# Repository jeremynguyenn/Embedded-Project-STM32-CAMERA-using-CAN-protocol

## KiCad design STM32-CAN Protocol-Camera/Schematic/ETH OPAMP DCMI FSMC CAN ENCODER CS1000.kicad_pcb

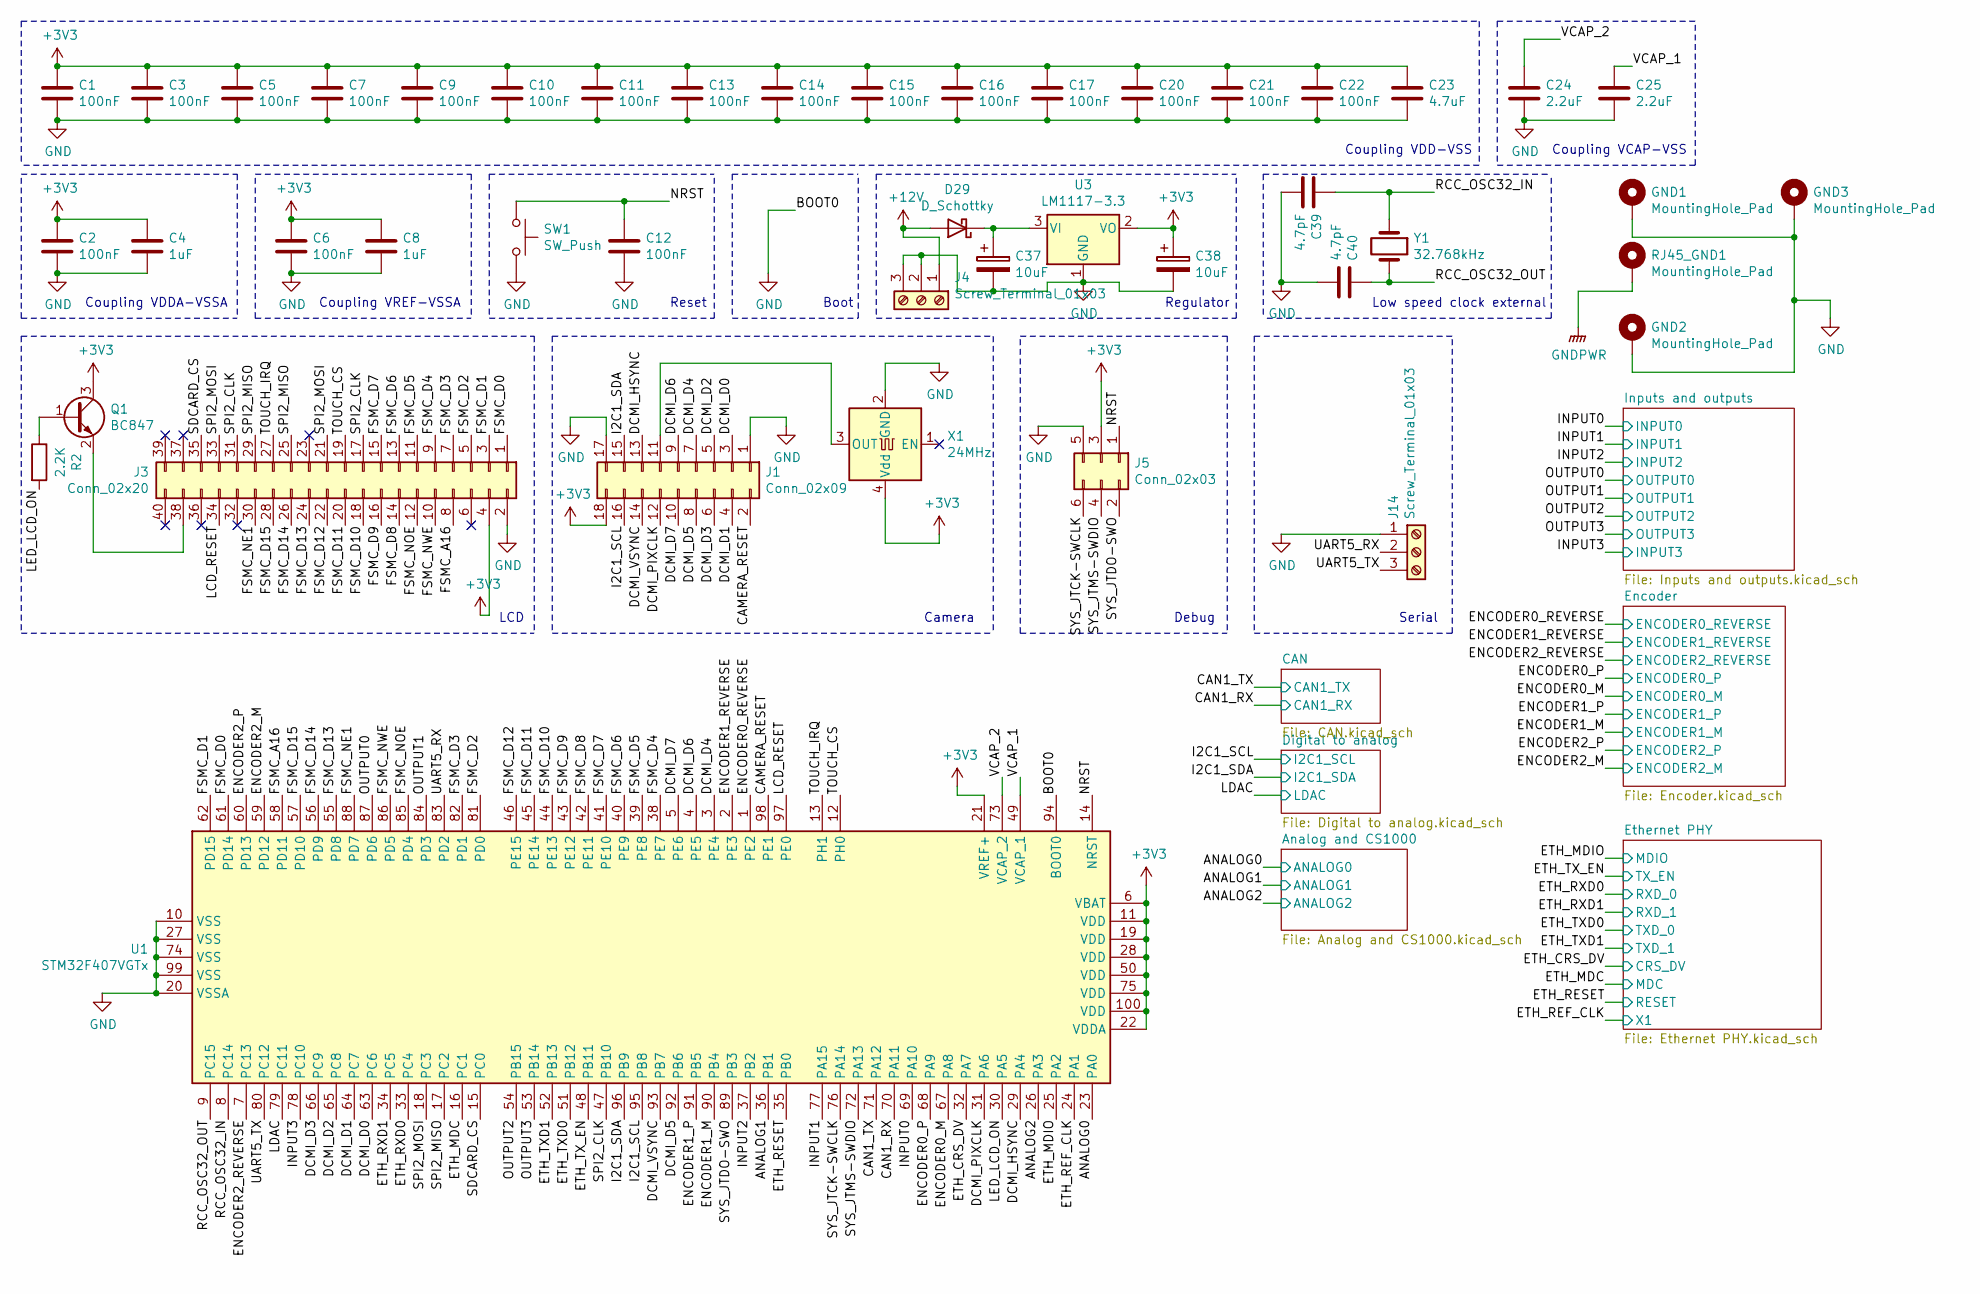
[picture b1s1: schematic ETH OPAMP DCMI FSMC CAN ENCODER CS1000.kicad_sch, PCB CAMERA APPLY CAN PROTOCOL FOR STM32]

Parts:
C1, C2, C3, C5, C6, C7, C9, C10, C11, C12, C13, C14, C15, C16, C17, C20, C21, C22: 100nF; C_0603_1608Metric
C4, C8: 1uF; C_0603_1608Metric
C23: 4.7uF; C_0603_1608Metric
C24, C25: 2.2uF; C_0603_1608Metric
C37, C38: 10uF; CP_EIA-1608-08_AVX-J_Pad1.25x1.05mm_HandSolder
C39, C40: 4.7pF; C_0603_1608Metric
D29: D_Schottky; D_SOD-123
GND1, GND2, GND3: MountingHole_Pad; MountingHole_2.7mm_M2.5_DIN965_Pad
J1: Conn_02x09; PinHeader_2x09_P2.54mm_Vertical
J3: Conn_02x20; PinHeader_2x20_P2.54mm_Vertical
J4, J14: Screw_Terminal_01x03; TerminalBlock_Phoenix_MKDS-1,5-3_1x03_P5.00mm_Horizontal
J5: Conn_02x03; PinHeader_2x03_P2.54mm_Vertical
Q1: BC847; SOT-23
R2: 2.2K; R_0603_1608Metric
RJ45_GND1: MountingHole_Pad; MountingHole_2.7mm_M2.5_DIN965_Pad
SW1: SW_Push; SW_SPST_FSMSM
U1: STM32F407VGTx; LQFP-100_14x14mm_P0.5mm
U3: LM1117-3.3; SOT-223
X1: 24MHz; Crystal_SMD_EuroQuartz_MT-4Pin_3.2x2.5mm_HandSoldering
Y1: 32.768kHz; Crystal_SMD_MicroCrystal_CC7V-T1A-2Pin_3.2x1.5mm_HandSolder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

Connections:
+3V3: C1.1, C2.1, C3.1, C4.1, C5.1, C6.1, C7.1, C8.1, C9.1, C10.1, C11.1, C13.1, C14.1, C15.1, C16.1, C17.1, C20.1, C21.1, C22.1, C23.1, C38.1, J1.18, J3.4, J5.3, Q1.3 (C), U1.6 (VBAT), U1.11 (VDD), U1.19 (VDD), U1.21 (VREF+), U1.22 (VDDA), U1.28 (VDD), U1.50 (VDD), U1.75 (VDD), U1.100 (VDD), U3.2 (VO), X1.4 (Vdd); also elsewhere on the board
+12V: D29.2 (A), J4.1
/ANALOG0: U1.23 (PA0); also elsewhere on the board
/ANALOG1: U1.36 (PB1); also elsewhere on the board
/ANALOG2: U1.26 (PA3); also elsewhere on the board
/CAMERA_RESET: J1.2, U1.98 (PE1)
/CAN1_RX: U1.70 (PA11); also elsewhere on the board
/CAN1_TX: U1.71 (PA12); also elsewhere on the board
/DCMI_D0: J1.3, U1.63 (PC6)
/DCMI_D1: J1.4, U1.64 (PC7)
/DCMI_D2: J1.5, U1.65 (PC8)
/DCMI_D3: J1.6, U1.66 (PC9)
/DCMI_D4: J1.7, U1.3 (PE4)
/DCMI_D5: J1.8, U1.92 (PB6)
/DCMI_D6: J1.9, U1.4 (PE5)
/DCMI_D7: J1.10, U1.5 (PE6)
/DCMI_HSYNC: J1.13, U1.29 (PA4)
/DCMI_PIXCLK: J1.12, U1.31 (PA6)
/DCMI_VSYNC: J1.14, U1.93 (PB7)
/ENCODER0_M: U1.67 (PA8); also elsewhere on the board
/ENCODER0_P: U1.68 (PA9); also elsewhere on the board
/ENCODER0_REVERSE: U1.1 (PE2); also elsewhere on the board
/ENCODER1_M: U1.90 (PB4); also elsewhere on the board
/ENCODER1_P: U1.91 (PB5); also elsewhere on the board
/ENCODER1_REVERSE: U1.2 (PE3); also elsewhere on the board
/ENCODER2_M: U1.59 (PD12); also elsewhere on the board
/ENCODER2_P: U1.60 (PD13); also elsewhere on the board
/ENCODER2_REVERSE: U1.7 (PC13); also elsewhere on the board
/ETH_CRS_DV: U1.32 (PA7); also elsewhere on the board
/ETH_MDC: U1.16 (PC1); also elsewhere on the board
/ETH_MDIO: U1.25 (PA2); also elsewhere on the board
/ETH_REF_CLK: U1.24 (PA1); also elsewhere on the board
/ETH_RESET: U1.35 (PB0); also elsewhere on the board
/ETH_RXD0: U1.33 (PC4); also elsewhere on the board
/ETH_RXD1: U1.34 (PC5); also elsewhere on the board
/ETH_TXD0: U1.51 (PB12); also elsewhere on the board
/ETH_TXD1: U1.52 (PB13); also elsewhere on the board
/ETH_TX_EN: U1.48 (PB11); also elsewhere on the board
/FSMC_A16: J3.8, U1.58 (PD11)
/FSMC_D0: J3.1, U1.61 (PD14)
/FSMC_D1: J3.3, U1.62 (PD15)
/FSMC_D2: J3.5, U1.81 (PD0)
/FSMC_D3: J3.7, U1.82 (PD1)
/FSMC_D4: J3.9, U1.38 (PE7)
/FSMC_D5: J3.11, U1.39 (PE8)
/FSMC_D6: J3.13, U1.40 (PE9)
/FSMC_D7: J3.15, U1.41 (PE10)
/FSMC_D8: J3.14, U1.42 (PE11)
/FSMC_D9: J3.16, U1.43 (PE12)
/FSMC_D10: J3.18, U1.44 (PE13)
/FSMC_D11: J3.20, U1.45 (PE14)
/FSMC_D12: J3.22, U1.46 (PE15)
/FSMC_D13: J3.24, U1.55 (PD8)
/FSMC_D14: J3.26, U1.56 (PD9)
/FSMC_D15: J3.28, U1.57 (PD10)
/FSMC_NE1: J3.30, U1.88 (PD7)
/FSMC_NOE: J3.12, U1.85 (PD4)
/FSMC_NWE: J3.10, U1.86 (PD5)
/I2C1_SCL: J1.16, U1.95 (PB8); also elsewhere on the board
/I2C1_SDA: J1.15, U1.96 (PB9); also elsewhere on the board
/INPUT0: U1.69 (PA10); also elsewhere on the board
/INPUT1: U1.77 (PA15); also elsewhere on the board
/INPUT2: U1.37 (PB2); also elsewhere on the board
/INPUT3: U1.78 (PC10); also elsewhere on the board
/LCD_RESET: J3.34, U1.97 (PE0)
/LDAC: U1.79 (PC11); also elsewhere on the board
/LED_LCD_ON: R2.2, U1.30 (PA5)
/NRST: C12.1, J5.1, SW1.1, U1.14 (NRST)
/OUTPUT0: U1.87 (PD6); also elsewhere on the board
/OUTPUT1: U1.84 (PD3); also elsewhere on the board
/OUTPUT2: U1.54 (PB15); also elsewhere on the board
/OUTPUT3: U1.53 (PB14); also elsewhere on the board
/RCC_OSC32_IN: C39.1, U1.8 (PC14), Y1.1
/RCC_OSC32_OUT: C40.1, U1.9 (PC15), Y1.2
/SDCARD_CS: J3.35, U1.15 (PC0)
/SPI2_CLK: J3.17, J3.31, U1.47 (PB10)
/SPI2_MISO: J3.25, J3.29, U1.17 (PC2)
/SPI2_MOSI: J3.21, J3.33, U1.18 (PC3)
/SYS_JTCK-SWCLK: J5.6, U1.76 (PA14)
/SYS_JTDO-SWO: J5.2, U1.89 (PB3)
/SYS_JTMS-SWDIO: J5.4, U1.72 (PA13)
/TOUCH_CS: J3.19, U1.12 (PH0)
/TOUCH_IRQ: J3.27, U1.13 (PH1)
/UART5_RX: J14.2, U1.83 (PD2)
/UART5_TX: J14.3, U1.80 (PC12)
/VCAP_1: C25.1, U1.49 (VCAP_1)
/VCAP_2: C24.1, U1.73 (VCAP_2)
GND: C1.2, C2.2, C3.2, C4.2, C5.2, C6.2, C7.2, C8.2, C9.2, C10.2, C11.2, C12.2, C13.2, C14.2, C15.2, C16.2, C17.2, C20.2, C21.2, C22.2, C23.2, C24.2, C25.2, C37.2, C38.2, C39.2, C40.2, GND1.1, GND2.1, GND3.1, J1.1, J1.17, J3.2, J4.2, J4.3, J5.5, J14.1, SW1.2, U1.10 (VSS), U1.20 (VSSA), U1.27 (VSS), U1.74 (VSS), U1.94 (BOOT0), U1.99 (VSS), U3.1 (GND), X1.2 (GND); also elsewhere on the board
GNDPWR: RJ45_GND1.1; also elsewhere on the board
unnamed: C37.1, D29.1 (K), U3.3 (VI)
unnamed: J1.11, X1.3 (OUT)
unnamed: J3.38, Q1.2 (E)
unnamed: Q1.1 (B), R2.1

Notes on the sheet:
Coupling VREF-VSSA
Camera
Boot
Low speed clock external
Regulator
Coupling VDD-VSS
Coupling VDDA-VSSA
Serial
LCD
Coupling VCAP-VSS
Reset
Debug

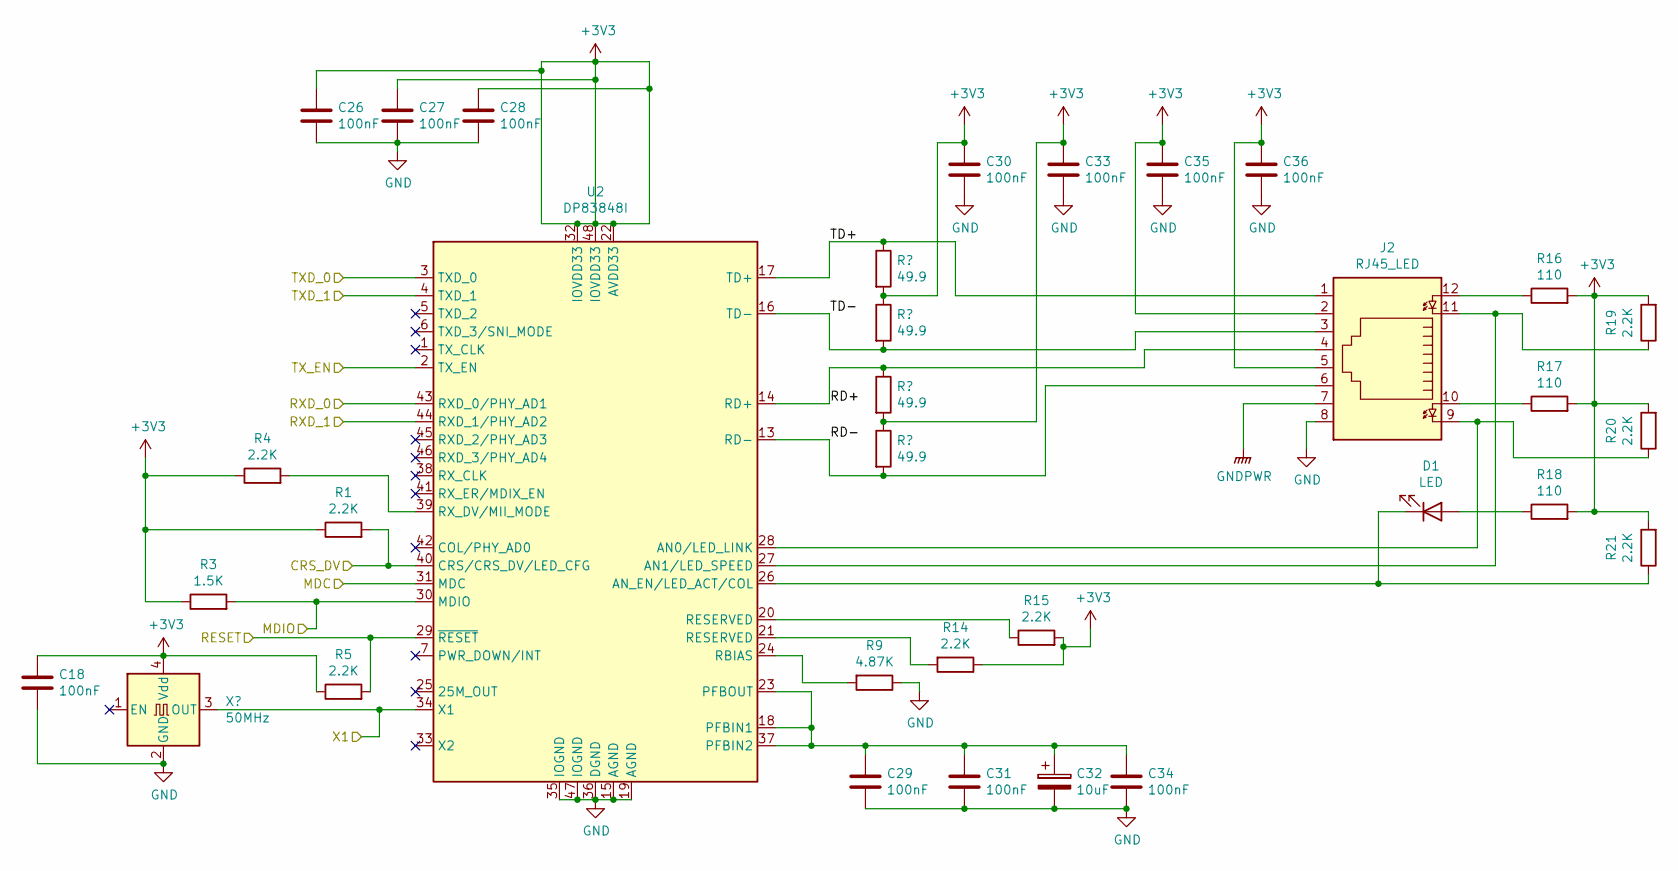
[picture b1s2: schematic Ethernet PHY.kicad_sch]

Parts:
C18, C26, C27, C28, C29, C30, C31, C33, C34, C35, C36: 100nF; C_0603_1608Metric
C32: 10uF; CP_EIA-1608-08_AVX-J_Pad1.25x1.05mm_HandSolder
D1: LED; LED_0603_1608Metric
J2: RJ45_LED; RJ45_Wuerth_7499010121A_Horizontal
R1, R4, R5, R14, R15, R19, R20, R21: 2.2K; R_0603_1608Metric
R3: 1.5K; R_0603_1608Metric
R9: 4.87K; R_0603_1608Metric
R10, R11, R12, R13: 49.9; R_0603_1608Metric
R16, R17, R18: 110; R_0603_1608Metric
U2: DP83848I; LQFP-48_7x7mm_P0.5mm
X2: 50MHz; Crystal_SMD_EuroQuartz_MT-4Pin_3.2x2.5mm_HandSoldering

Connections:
+3V3: C18.1, C26.1, C27.1, C28.1, C30.1, C33.1, C35.1, C36.1, J2.2, J2.5, R1.1, R3.1, R4.1, R5.1, R10.2, R11.1, R12.2, R13.1, R14.1, R15.2, R16.2, R17.2, R18.2, R19.2, R20.2, R21.2, U2.22 (AVDD33), U2.32 (IOVDD33), U2.48 (IOVDD33), X2.4 (Vdd); also elsewhere on the board
/ETH_CRS_DV: R1.2, U2.40 (CRS/CRS_DV/LED_CFG); also elsewhere on the board
/ETH_MDC: U2.31 (MDC); also elsewhere on the board
/ETH_MDIO: R3.2, U2.30 (MDIO); also elsewhere on the board
/ETH_REF_CLK: U2.34 (X1), X2.3 (OUT); also elsewhere on the board
/ETH_RESET: R5.2, U2.29 (~RESET); also elsewhere on the board
/ETH_RXD0: U2.43 (RXD_0/PHY_AD1); also elsewhere on the board
/ETH_RXD1: U2.44 (RXD_1/PHY_AD2); also elsewhere on the board
/ETH_TXD0: U2.3 (TXD_0); also elsewhere on the board
/ETH_TXD1: U2.4 (TXD_1); also elsewhere on the board
/ETH_TX_EN: U2.2 (TX_EN); also elsewhere on the board
/Ethernet PHY/RD+: J2.4, R12.1, U2.14 (RD+)
/Ethernet PHY/RD-: J2.6, R13.2, U2.13 (RD-)
/Ethernet PHY/TD+: J2.1, R10.1, U2.17 (TD+)
/Ethernet PHY/TD-: J2.3, R11.2, U2.16 (TD-)
GND: C18.2, C26.2, C27.2, C28.2, C29.2, C30.2, C31.2, C32.2, C33.2, C34.2, C35.2, C36.2, J2.8, R9.1, U2.15 (AGND), U2.19 (AGND), U2.35 (IOGND), U2.36 (DGND), U2.47 (IOGND), X2.2 (GND); also elsewhere on the board
GNDPWR: J2.7; also elsewhere on the board
unnamed: C29.1, C31.1, C32.1, C34.1, U2.18 (PFBIN1), U2.23 (PFBOUT), U2.37 (PFBIN2)
unnamed: D1.1 (K), R21.1, U2.26 (AN_EN/LED_ACT/COL)
unnamed: D1.2 (A), R18.1
unnamed: J2.9, R20.1, U2.28 (AN0/LED_LINK)
unnamed: J2.10, R17.1
unnamed: J2.11, R19.1, U2.27 (AN1/LED_SPEED)
unnamed: J2.12, R16.1
unnamed: R4.2, U2.39 (RX_DV/MII_MODE)
unnamed: R9.2, U2.24 (RBIAS)
unnamed: R14.2, U2.21 (RESERVED)
unnamed: R15.1, U2.20 (RESERVED)

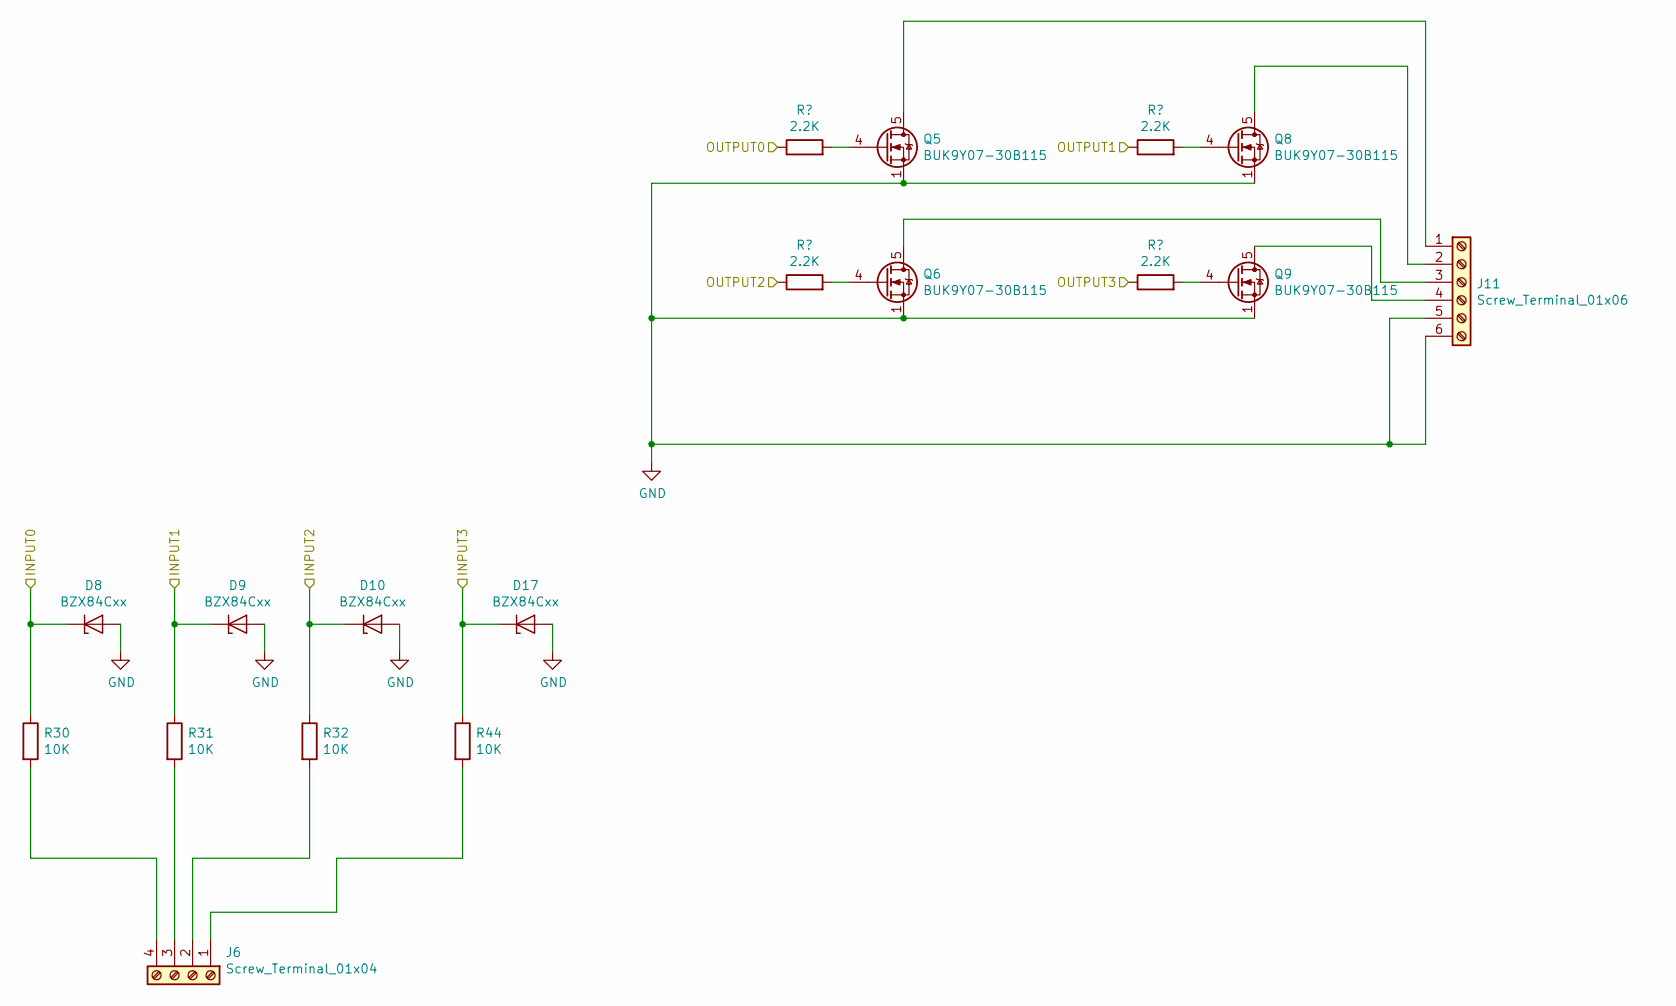
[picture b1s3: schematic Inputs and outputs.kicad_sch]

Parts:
D8, D9, D10, D17: BZX84Cxx; D_SOT-23_ANK
J6: Screw_Terminal_01x04; TerminalBlock_Phoenix_MKDS-1,5-4_1x04_P5.00mm_Horizontal
J11: Screw_Terminal_01x06; TerminalBlock_Phoenix_MKDS-1,5-6_1x06_P5.00mm_Horizontal
Q5, Q6, Q8, Q9: BUK9Y07-30B115; LFPAK56
R30, R31, R32, R44: 10K; R_0603_1608Metric
R33, R34, R36, R37: 2.2K; R_0603_1608Metric

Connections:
/INPUT0: D8.1 (K), R30.1; also elsewhere on the board
/INPUT1: D9.1 (K), R31.1; also elsewhere on the board
/INPUT2: D10.1 (K), R32.1; also elsewhere on the board
/INPUT3: D17.1 (K), R44.1; also elsewhere on the board
/OUTPUT0: R33.1; also elsewhere on the board
/OUTPUT1: R36.1; also elsewhere on the board
/OUTPUT2: R34.1; also elsewhere on the board
/OUTPUT3: R37.1; also elsewhere on the board
GND: D8.2 (A), D9.2 (A), D10.2 (A), D17.2 (A), J11.5, J11.6, Q5.1 (S), Q5.2 (S), Q5.3 (S), Q6.1 (S), Q6.2 (S), Q6.3 (S), Q8.1 (S), Q8.2 (S), Q8.3 (S), Q9.1 (S), Q9.2 (S), Q9.3 (S); also elsewhere on the board
unnamed: J6.1, R44.2
unnamed: J6.2, R32.2
unnamed: J6.3, R31.2
unnamed: J6.4, R30.2
unnamed: J11.1, Q5.5 (D)
unnamed: J11.2, Q8.5 (D)
unnamed: J11.3, Q6.5 (D)
unnamed: J11.4, Q9.5 (D)
unnamed: Q5.4 (G), R33.2
unnamed: Q6.4 (G), R34.2
unnamed: Q8.4 (G), R36.2
unnamed: Q9.4 (G), R37.2

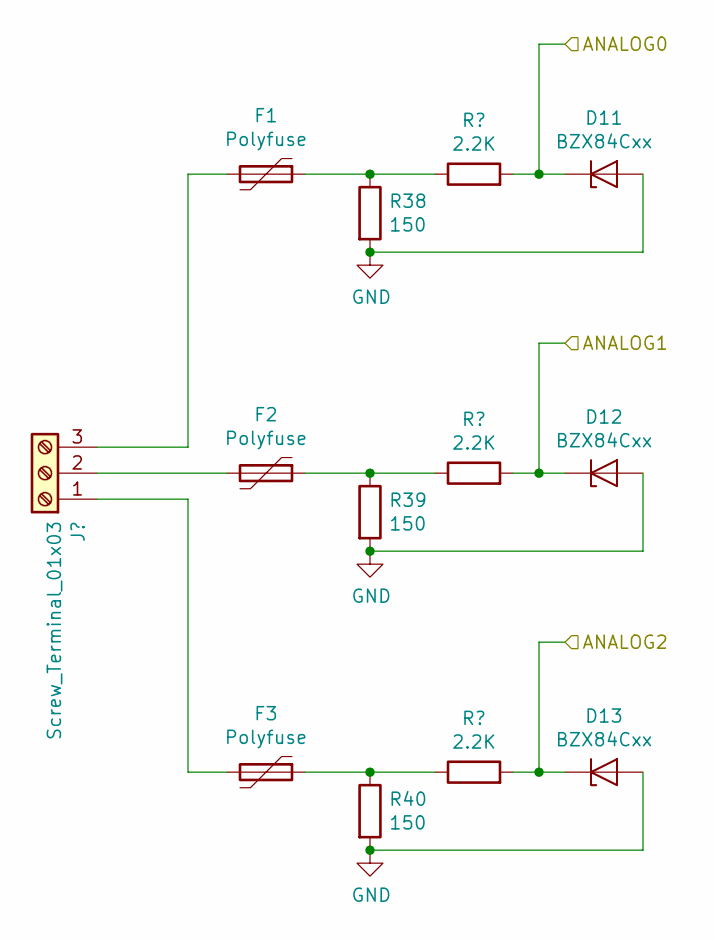
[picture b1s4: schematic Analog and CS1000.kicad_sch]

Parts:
D11, D12, D13: BZX84Cxx; D_SOT-23_ANK
F1, F2, F3: Polyfuse; R_0603_1608Metric
J12: Screw_Terminal_01x03; TerminalBlock_Phoenix_MKDS-1,5-3_1x03_P5.00mm_Horizontal
R38, R39, R40: 150; R_1206_3216Metric
R41, R42, R43: 2.2K; R_0603_1608Metric

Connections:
/ANALOG0: D11.1 (K), R41.2; also elsewhere on the board
/ANALOG1: D12.1 (K), R42.2; also elsewhere on the board
/ANALOG2: D13.1 (K), R43.2; also elsewhere on the board
GND: D11.2 (A), D12.2 (A), D13.2 (A), R38.2, R39.2, R40.2; also elsewhere on the board
unnamed: F1.1, R38.1, R41.1
unnamed: F1.2, J12.3
unnamed: F2.1, R39.1, R42.1
unnamed: F2.2, J12.2
unnamed: F3.1, R40.1, R43.1
unnamed: F3.2, J12.1

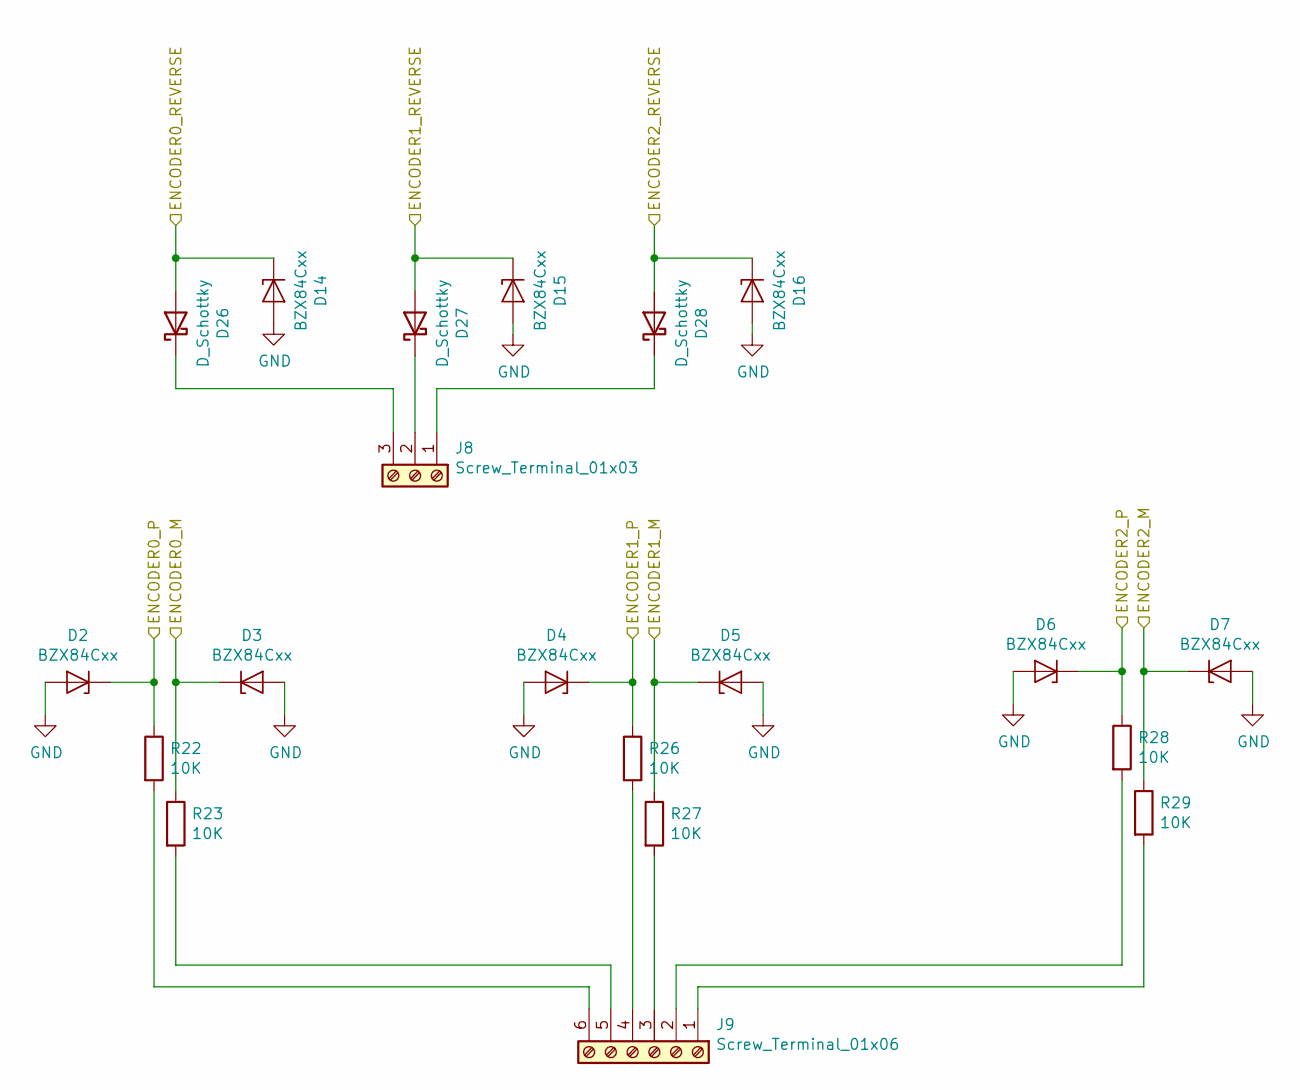
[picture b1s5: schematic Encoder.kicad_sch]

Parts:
D2, D3, D4, D5, D6, D7, D14, D15, D16: BZX84Cxx; D_SOT-23_ANK
D26, D27, D28: D_Schottky; D_SOD-123
J8: Screw_Terminal_01x03; TerminalBlock_Phoenix_MKDS-1,5-3_1x03_P5.00mm_Horizontal
J9: Screw_Terminal_01x06; TerminalBlock_Phoenix_MKDS-1,5-6_1x06_P5.00mm_Horizontal
R22, R23, R26, R27, R28, R29: 10K; R_0603_1608Metric

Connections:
/ENCODER0_M: D3.1 (K), R23.1; also elsewhere on the board
/ENCODER0_P: D2.1 (K), R22.1; also elsewhere on the board
/ENCODER0_REVERSE: D14.1 (K), D26.2 (A); also elsewhere on the board
/ENCODER1_M: D5.1 (K), R27.1; also elsewhere on the board
/ENCODER1_P: D4.1 (K), R26.1; also elsewhere on the board
/ENCODER1_REVERSE: D15.1 (K), D27.2 (A); also elsewhere on the board
/ENCODER2_M: D7.1 (K), R29.1; also elsewhere on the board
/ENCODER2_P: D6.1 (K), R28.1; also elsewhere on the board
/ENCODER2_REVERSE: D16.1 (K), D28.2 (A); also elsewhere on the board
GND: D2.2 (A), D3.2 (A), D4.2 (A), D5.2 (A), D6.2 (A), D7.2 (A), D14.2 (A), D15.2 (A), D16.2 (A); also elsewhere on the board
unnamed: D26.1 (K), J8.3
unnamed: D27.1 (K), J8.2
unnamed: D28.1 (K), J8.1
unnamed: J9.1, R29.2
unnamed: J9.2, R28.2
unnamed: J9.3, R27.2
unnamed: J9.4, R26.2
unnamed: J9.5, R23.2
unnamed: J9.6, R22.2

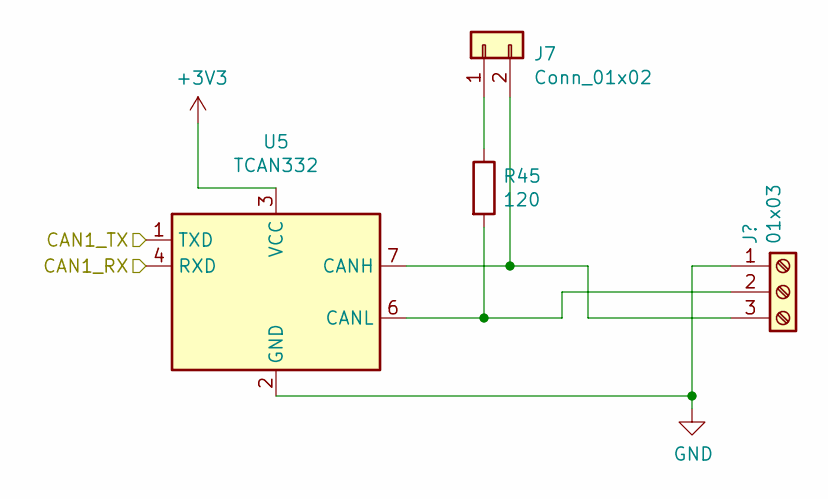
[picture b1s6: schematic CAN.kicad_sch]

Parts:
J7: Conn_01x02; PinHeader_1x02_P2.54mm_Vertical
J10: 01x03; TerminalBlock_Phoenix_MKDS-1,5-3_1x03_P5.00mm_Horizontal
R45: 120; R_0603_1608Metric
U5: TCAN332; SOIC-8_3.9x4.9mm_P1.27mm

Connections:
+3V3: U5.3 (VCC); also elsewhere on the board
/CAN1_RX: U5.4 (RXD); also elsewhere on the board
/CAN1_TX: U5.1 (TXD); also elsewhere on the board
GND: J10.1, U5.2 (GND); also elsewhere on the board
unnamed: J7.1, R45.1
unnamed: J10.2, R45.2, U5.6 (CANL)
unnamed: J7.2, J10.3, U5.7 (CANH)

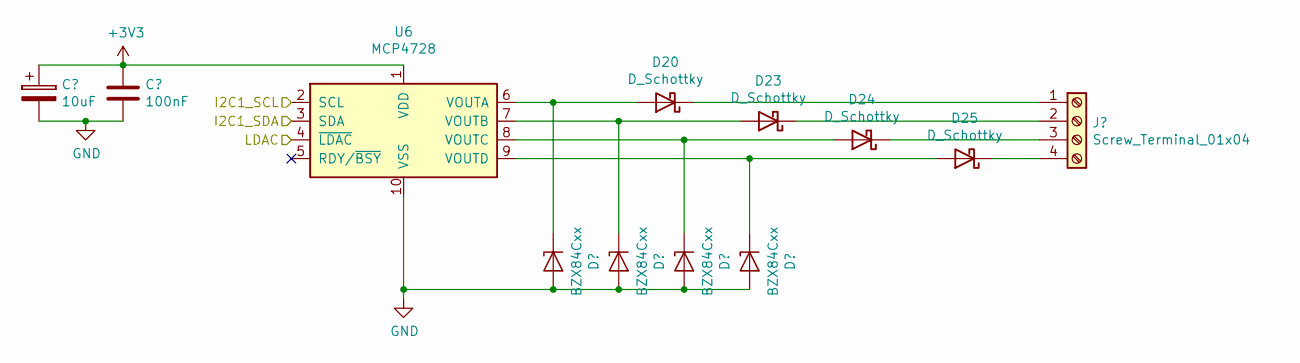
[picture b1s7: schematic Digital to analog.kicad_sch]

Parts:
C41: 10uF; CP_EIA-1608-08_AVX-J_Pad1.25x1.05mm_HandSolder
C42: 100nF; C_0603_1608Metric
D18, D19, D21, D22: BZX84Cxx; D_SOT-23_ANK
D20, D23, D24, D25: D_Schottky; D_SOD-123
J13: Screw_Terminal_01x04; TerminalBlock_Phoenix_MKDS-1,5-4_1x04_P5.00mm_Horizontal
U6: MCP4728; MSOP-10_3x3mm_P0.5mm

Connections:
+3V3: C41.1, C42.1, U6.1 (VDD); also elsewhere on the board
/I2C1_SCL: U6.2 (SCL); also elsewhere on the board
/I2C1_SDA: U6.3 (SDA); also elsewhere on the board
/LDAC: U6.4 (~LDAC); also elsewhere on the board
GND: C41.2, C42.2, D18.2 (A), D19.2 (A), D21.2 (A), D22.2 (A), U6.10 (VSS); also elsewhere on the board
unnamed: D18.1 (K), D20.2 (A), U6.6 (VOUTA)
unnamed: D19.1 (K), D23.2 (A), U6.7 (VOUTB)
unnamed: D20.1 (K), J13.1
unnamed: D21.1 (K), D24.2 (A), U6.8 (VOUTC)
unnamed: D22.1 (K), D25.2 (A), U6.9 (VOUTD)
unnamed: D23.1 (K), J13.2
unnamed: D24.1 (K), J13.3
unnamed: D25.1 (K), J13.4

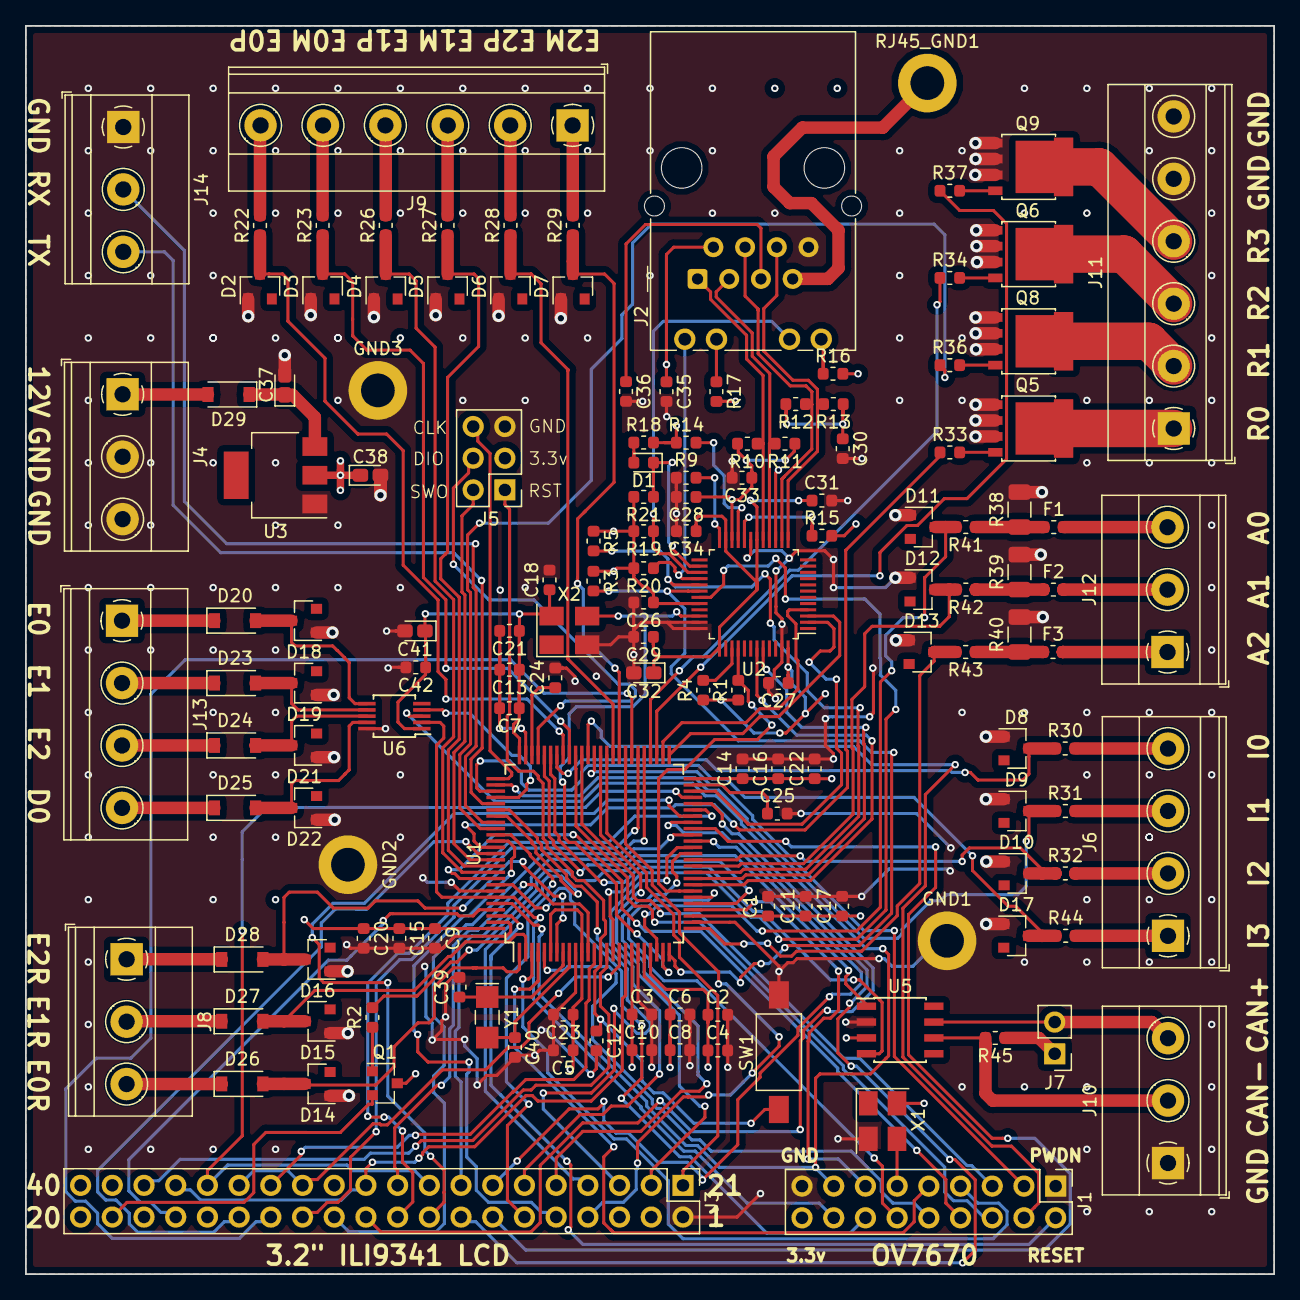
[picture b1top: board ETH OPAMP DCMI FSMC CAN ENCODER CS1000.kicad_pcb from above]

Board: 4 copper layers, 100.0 x 100.0 mm, 144 parts (0 on the bottom side), 146 nets.

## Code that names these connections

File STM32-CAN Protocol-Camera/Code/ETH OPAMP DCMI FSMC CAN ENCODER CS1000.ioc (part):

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Mcu.Name=STM32F407V(E-G)Tx
Mcu.Package=LQFP100
Mcu.UserName=STM32F407VGTx
PA0-WKUP.GPIOParameters=GPIO_Label
PA0-WKUP.GPIO_Label=ANALOG0
PA0-WKUP.Signal=ADCx_IN0
PA1.Mode=RMII
PA1.Signal=ETH_REF_CLK
PA10.GPIOParameters=GPIO_Label
PA10.GPIO_Label=INPUT0
PA10.Signal=GPIO_Input
PA11.Mode=CAN_Activate
PA11.Signal=CAN1_RX
PA12.Mode=CAN_Activate
PA12.Signal=CAN1_TX
PA13.Mode=Trace_Asynchronous_SW
PA13.Signal=SYS_JTMS-SWDIO
PA14.Mode=Trace_Asynchronous_SW
PA14.Signal=SYS_JTCK-SWCLK
PA15.GPIOParameters=GPIO_Label
PA15.GPIO_Label=INPUT1
PA15.Signal=GPIO_Input
PA2.Mode=RMII
PA2.Signal=ETH_MDIO
PA3.GPIOParameters=GPIO_Label
PA3.GPIO_Label=ANALOG2
PA3.Signal=ADCx_IN3
PA4.Mode=Slave_8_bits_External_Synchro
PA4.Signal=DCMI_HSYNC
PA5.GPIOParameters=GPIO_Label
PA5.GPIO_Label=LED_LCD_ON
PA5.Signal=GPIO_Output
PA6.Mode=Slave_8_bits_External_Synchro
PA6.Signal=DCMI_PIXCLK
PA7.Mode=RMII
PA7.Signal=ETH_CRS_DV
PA8.GPIOParameters=GPIO_Label
PA8.GPIO_Label=ENCODER0_M
PA8.Signal=S_TIM1_CH1
PA9.GPIOParameters=GPIO_Label
PA9.GPIO_Label=ENCODER0_P
PA9.Signal=S_TIM1_CH2
PB0.GPIOParameters=GPIO_Label
PB0.GPIO_Label=ETH_RESET
PB0.Signal=GPIO_Output
PB1.GPIOParameters=GPIO_Label
PB1.GPIO_Label=ANALOG1
PB1.Signal=ADCx_IN9
PB10.Mode=Full_Duplex_Master
PB10.Signal=SPI2_SCK
PB11.Mode=RMII
PB11.Signal=ETH_TX_EN
PB12.GPIOParameters=GPIO_PuPd
PB12.GPIO_PuPd=GPIO_NOPULL
PB12.Mode=RMII
PB12.Signal=ETH_TXD0
PB13.GPIOParameters=GPIO_PuPd
PB13.GPIO_PuPd=GPIO_NOPULL
PB13.Mode=RMII
PB13.Signal=ETH_TXD1
PB14.GPIOParameters=GPIO_Label
PB14.GPIO_Label=OUTPUT3
PB14.Signal=GPIO_Output
PB15.GPIOParameters=GPIO_Label
PB15.GPIO_Label=OUTPUT2
PB15.Signal=GPIO_Output
PB2.GPIOParameters=GPIO_Label
PB2.GPIO_Label=INPUT2
PB2.Signal=GPIO_Input
PB3.Mode=Trace_Asynchronous_SW
PB3.Signal=SYS_JTDO-SWO
PB4.GPIOParameters=GPIO_Label
PB4.GPIO_Label=ENCODER1_M
PB4.Signal=S_TIM3_CH1
PB5.GPIOParameters=GPIO_Label
PB5.GPIO_Label=ENCODER1_P
PB5.Signal=S_TIM3_CH2
PB6.Mode=Slave_8_bits_External_Synchro
PB6.Signal=DCMI_D5
PB7.Mode=Slave_8_bits_External_Synchro
PB7.Signal=DCMI_VSYNC
PB8.GPIOParameters=GPIO_Pu
PB8.GPIO_Pu=GPIO_PULLUP
PB8.Mode=I2C
PB8.Signal=I2C1_SCL
PB9.GPIOParameters=GPIO_Pu
PB9.GPIO_Pu=GPIO_PULLUP
PB9.Mode=I2C
PB9.Signal=I2C1_SDA
PC0.GPIOParameters=GPIO_Label
PC0.GPIO_Label=SDCARD_CS
PC0.Signal=GPIO_Output
PC1.Mode=RMII
PC1.Signal=ETH_MDC
PC10.GPIOParameters=GPIO_Label
PC10.GPIO_Label=INPUT3
PC10.Signal=GPIO_Input
PC11.GPIOParameters=GPIO_PuPd,GPIO_Label
PC11.GPIO_Label=LDAC
PC11.GPIO_PuPd=GPIO_PULLUP
PC11.Signal=GPIO_Output
PC12.Mode=Asynchronous
PC12.Signal=UART5_TX
PC13-ANTI_TAMP.GPIOParameters=GPIO_Label
PC13-ANTI_TAMP.GPIO_Label=ENCODER2_REVERSE
PC13-ANTI_TAMP.Signal=GPIO_Output
PC14-OSC32_IN.Mode=LSE-External-Oscillator
PC14-OSC32_IN.Signal=RCC_OSC32_IN
PC15-OSC32_OUT.Mode=LSE-External-Oscillator
PC15-OSC32_OUT.Signal=RCC_OSC32_OUT
PC2.Mode=Full_Duplex_Master
PC2.Signal=SPI2_MISO
PC3.Mode=Full_Duplex_Master
PC3.Signal=SPI2_MOSI
PC4.GPIOParameters=GPIO_PuPd
PC4.GPIO_PuPd=GPIO_PULLDOWN
PC4.Mode=RMII
PC4.Signal=ETH_RXD0
PC5.GPIOParameters=GPIO_PuPd
PC5.GPIO_PuPd=GPIO_PULLDOWN
PC5.Mode=RMII
PC5.Signal=ETH_RXD1
PC6.Mode=Slave_8_bits_External_Synchro
PC6.Signal=DCMI_D0
PC7.Mode=Slave_8_bits_External_Synchro
PC7.Signal=DCMI_D1
PC8.Mode=Slave_8_bits_External_Synchro
PC8.Signal=DCMI_D2
PC9.Mode=Slave_8_bits_External_Synchro
PC9.Signal=DCMI_D3
PD0.Mode=16b-d1
PD0.Signal=FSMC_D2
PD1.Mode=16b-d1
PD1.Signal=FSMC_D3
PD10.Mode=16b-d1
PD10.Signal=FSMC_D15
PD11.Mode=A16_1
PD11.Signal=FSMC_A16
PD12.GPIOParameters=GPIO_Label
PD12.GPIO_Label=ENCODER2_M
PD12.Signal=S_TIM4_CH1
PD13.GPIOParameters=GPIO_Label
PD13.GPIO_Label=ENCODER2_P
PD13.Signal=S_TIM4_CH2
PD14.Mode=16b-d1
PD14.Signal=FSMC_D0
PD15.Mode=16b-d1
PD15.Signal=FSMC_D1
PD2.Mode=Asynchronous
PD2.Signal=UART5_RX
PD3.GPIOParameters=GPIO_Label
PD3.GPIO_Label=OUTPUT1
PD3.Signal=GPIO_Output
PD4.Mode=Lcd1
PD4.Signal=FSMC_NOE
PD5.Mode=Lcd1
PD5.Signal=FSMC_NWE
PD6.GPIOParameters=GPIO_Label
PD6.GPIO_Label=OUTPUT0
PD6.Signal=GPIO_Output
PD7.Mode=NorPsramChipSelect1_1
PD7.Signal=FSMC_NE1
PD8.Mode=16b-d1
PD8.Signal=FSMC_D13
PD9.Mode=16b-d1
PD9.Signal=FSMC_D14
PE0.GPIOParameters=GPIO_Label
PE0.GPIO_Label=LCD_RESET
PE0.Signal=GPIO_Output
PE1.GPIOParameters=GPIO_Label
PE1.GPIO_Label=CAMERA_RESET
PE1.Signal=GPIO_Output
PE10.Mode=16b-d1
PE10.Signal=FSMC_D7
PE11.Mode=16b-d1
PE11.Signal=FSMC_D8
PE12.Mode=16b-d1
PE12.Signal=FSMC_D9
PE13.Mode=16b-d1
PE13.Signal=FSMC_D10
PE14.Mode=16b-d1
PE14.Signal=FSMC_D11
PE15.Mode=16b-d1
PE15.Signal=FSMC_D12
PE2.GPIOParameters=GPIO_Label
PE2.GPIO_Label=ENCODER0_REVERSE
PE2.Signal=GPIO_Output
PE3.GPIOParameters=GPIO_Label
PE3.GPIO_Label=ENCODER1_REVERSE
PE3.Signal=GPIO_Output
PE4.Mode=Slave_8_bits_External_Synchro
PE4.Signal=DCMI_D4
PE5.Mode=Slave_8_bits_External_Synchro
PE5.Signal=DCMI_D6
PE6.Mode=Slave_8_bits_External_Synchro
PE6.Signal=DCMI_D7
PE7.Mode=16b-d1
PE7.Signal=FSMC_D4
PE8.Mode=16b-d1
PE8.Signal=FSMC_D5
PE9.Mode=16b-d1
PE9.Signal=FSMC_D6
PH0-OSC_IN.GPIOParameters=GPIO_Label
PH0-OSC_IN.GPIO_Label=TOUCH_CS
PH0-OSC_IN.Signal=GPIO_Output
PH1-OSC_OUT.GPIOParameters=GPIO_Label
PH1-OSC_OUT.GPIO_Label=TOUCH_IRQ
PH1-OSC_OUT.Signal=GPIO_Input
RCC.HSE_VALUE=4000000
RCC.SYSCLKFreq_VALUE=50000000
RCC.SYSCLKSource=RCC_SYSCLKSOURCE_PLLCLK
board=custom

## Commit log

2024-11-27 project init
2024-11-27 Create LISCENSE
2024-11-27 Create LICENSE
